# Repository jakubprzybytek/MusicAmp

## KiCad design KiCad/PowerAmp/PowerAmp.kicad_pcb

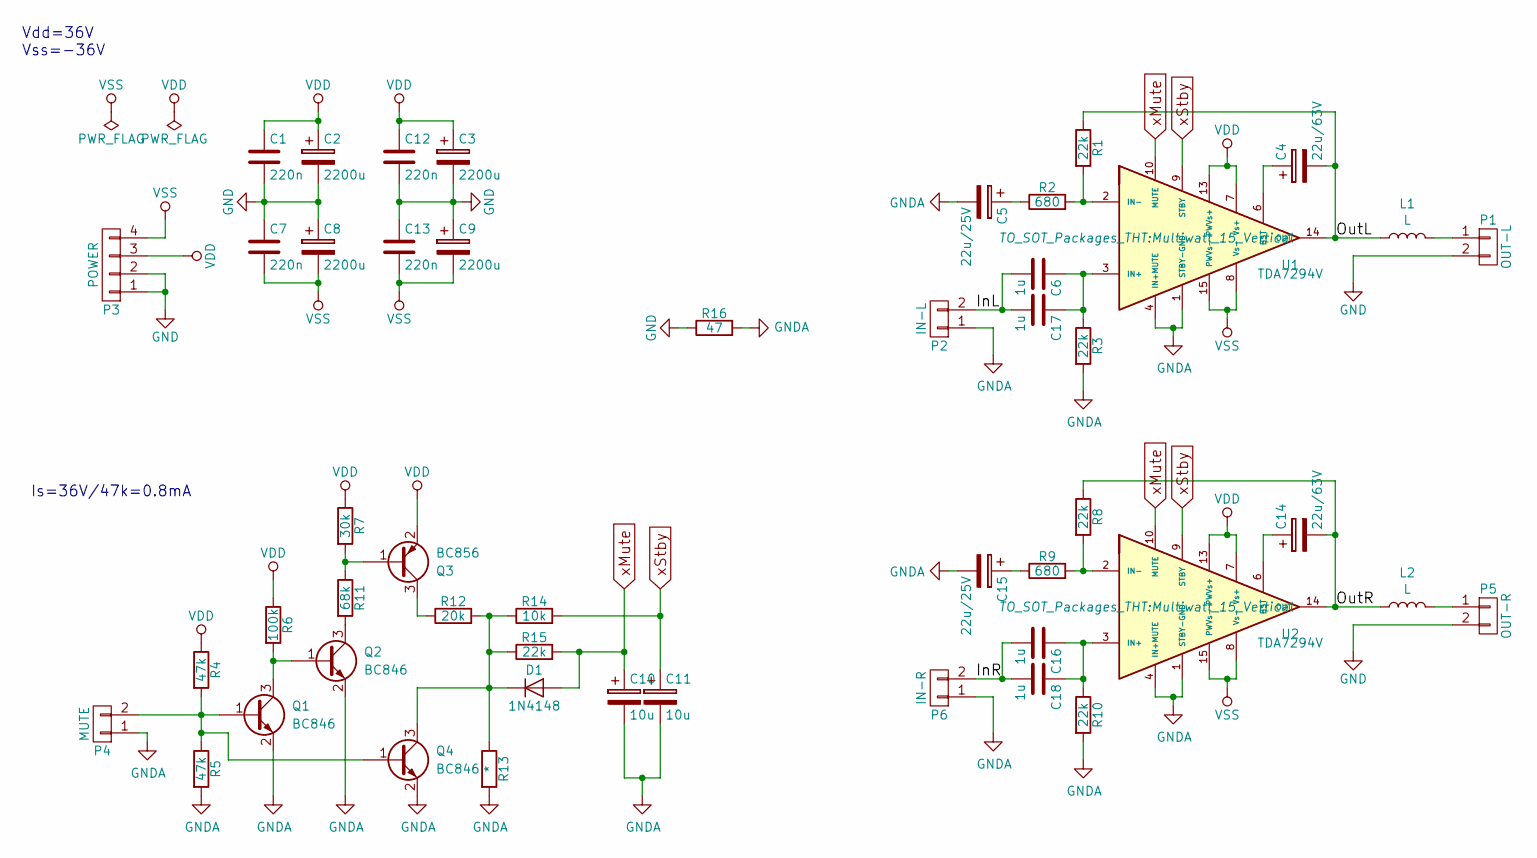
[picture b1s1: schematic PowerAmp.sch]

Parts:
C1, C7, C12, C13: 220n; C_0805_2012Metric
C2, C3, C8, C9: 2200u; CP_Radial_D18.0mm_P7.50mm
C4: 22u/63V; CP_Radial_D5.0mm_P2.00mm
C5, C15: 22u/25V; CP_EIA-6032-28_Kemet-C
C6, C16, C17, C18: 1u; C_2220_5650Metric
C10, C11: 10u; CP_Radial_D5.0mm_P2.00mm
C14: 22u/63V; CP_Radial_D5.0mm_P2.50mm
D1: 1N4148; D_MiniMELF
L1, L2: L; L_Axial_L9.5mm_D4.0mm_P12.70mm_Horizontal_Fastron_SMCC
P1: OUT-L; Molex_Mini-Fit_Jr_5566-02A_2x01_P4.20mm_Vertical
P2: IN-L; Molex_Micro-Latch_53253-0270_1x02_P2.00mm_Vertical
P3: POWER; Molex_Mini-Fit_Jr_5566-04A_2x02_P4.20mm_Vertical
P4: MUTE; Molex_Micro-Latch_53253-0270_1x02_P2.00mm_Vertical
P5: OUT-R; Molex_Mini-Fit_Jr_5566-02A_2x01_P4.20mm_Vertical
P6: IN-R; Molex_Micro-Latch_53253-0270_1x02_P2.00mm_Vertical
Q1, Q2, Q4: BC846; SOT-23
Q3: BC856; SOT-23
R1, R3, R8, R10, R15: 22k; R_0805_2012Metric
R2, R9: 680; R_0805_2012Metric
R4, R5: 47k; R_0805_2012Metric
R6: 100k; R_0805_2012Metric
R7: 30k; R_0805_2012Metric
R11: 68k; R_0805_2012Metric
R12: 20k; R_0805_2012Metric
R13: *; R_0805_2012Metric
R14: 10k; R_0805_2012Metric
R16: 47; R_0805_2012Metric
U1, U2: TDA7294V; Multiwatt_15_Vertical

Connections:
/InL: C6.2, C17.2, P2.2
/InR: C16.2, C18.2, P6.2
/OutL: C4.2, L1.1, R1.1, U1.14 (OUT)
/OutR: C14.2, L2.1, R8.1, U2.14 (OUT)
GND: C1.2, C2.2, C3.2, C7.1, C8.1, C9.1, C12.2, C13.1, P1.2, P3.1, P3.2, P5.2, R16.1
GNDA: C5.2, C10.2, C11.2, C15.2, P2.1, P4.1, P6.1, Q1.2 (E), Q2.2 (E), Q4.2 (E), R3.2, R5.2, R10.2, R13.2, R16.2, U1.1 (STBY-GND), U1.4 (IN+MUTE), U2.1 (STBY-GND), U2.4 (IN+MUTE)
unnamed: C4.1, U1.6 (BST)
unnamed: C5.1, R2.1
unnamed: C14.1, U2.6 (BST)
unnamed: C15.1, R9.1
unnamed: C16.1, C18.1, R10.1, U2.3 (IN+)
unnamed: C6.1, C17.1, R3.1, U1.3 (IN+)
unnamed: D1.1 (K), Q4.3 (C), R12.2, R13.1, R14.1, R15.1
unnamed: L1.2, P1.1
unnamed: L2.2, P5.1
unnamed: P4.2, Q1.1 (B), Q4.1 (B), R4.2, R5.1
unnamed: Q1.3 (C), Q2.1 (B), R6.2
unnamed: Q2.3 (C), R11.2
unnamed: Q3.1 (B), R7.2, R11.1
unnamed: Q3.3 (C), R12.1
unnamed: R1.2, R2.2, U1.2 (IN-)
unnamed: R8.2, R9.2, U2.2 (IN-)
VDD: C1.1, C2.1, C3.1, C12.1, P3.3, Q3.2 (E), R4.1, R6.1, R7.1, U1.7 (Vs+), U1.13 (PWVs+), U2.7 (Vs+), U2.13 (PWVs+)
VSS: C7.2, C8.2, C9.2, C13.2, P3.4, U1.8 (Vs-), U1.15 (PWVs-), U2.8 (Vs-), U2.15 (PWVs-)
xMute: C10.1, D1.2 (A), R15.2, U1.10 (MUTE), U2.10 (MUTE)
xStby: C11.1, R14.2, U1.9 (STBY), U2.9 (STBY)

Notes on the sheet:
Vdd=36V Vss=-36V
Is=36V/47k=0.8mA

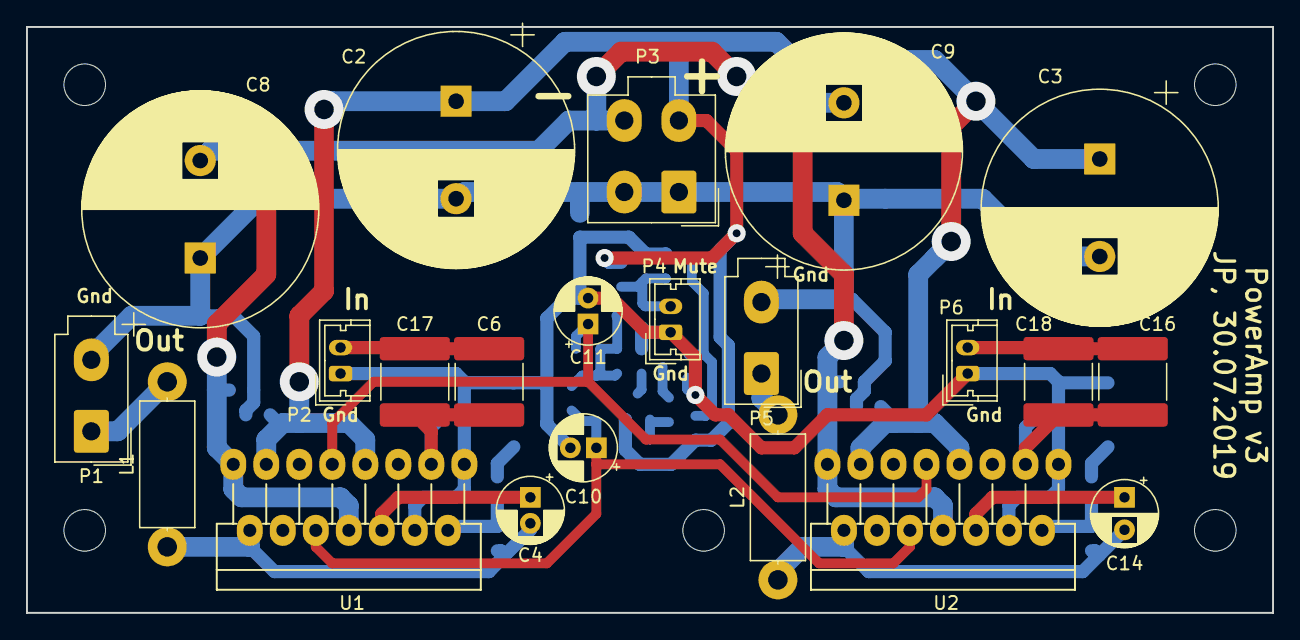
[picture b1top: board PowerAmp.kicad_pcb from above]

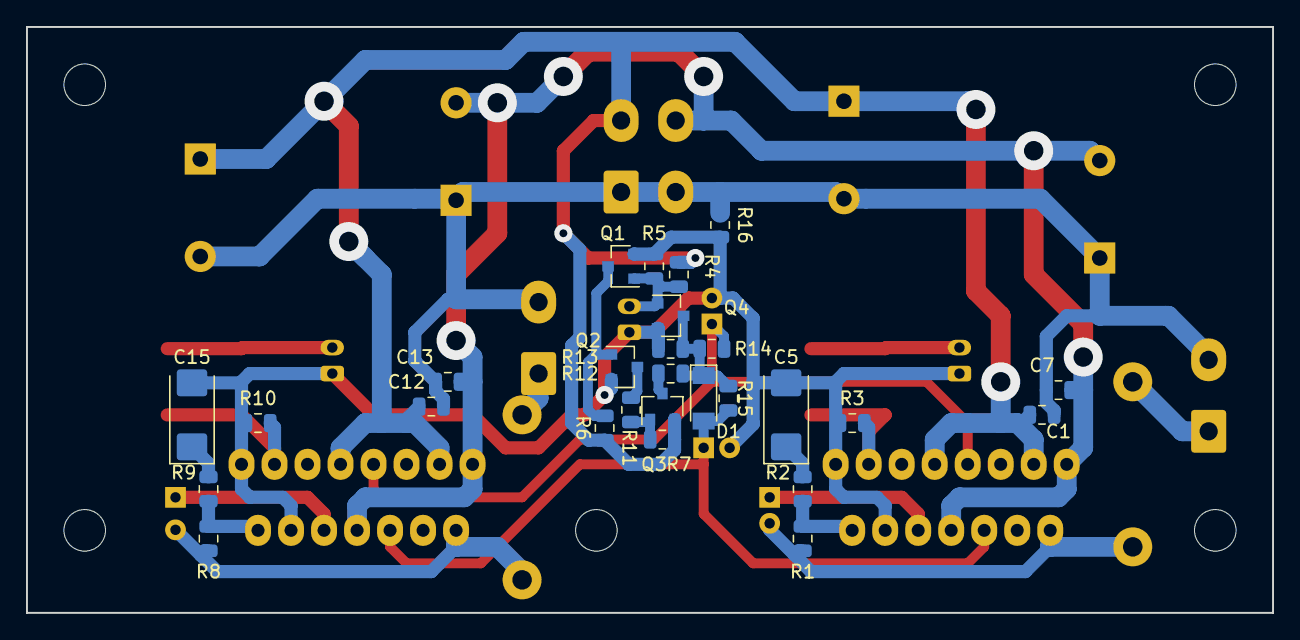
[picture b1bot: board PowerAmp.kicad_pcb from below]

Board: 2 copper layers, 95.9 x 45.1 mm, 49 parts (27 on the bottom side), 26 nets.

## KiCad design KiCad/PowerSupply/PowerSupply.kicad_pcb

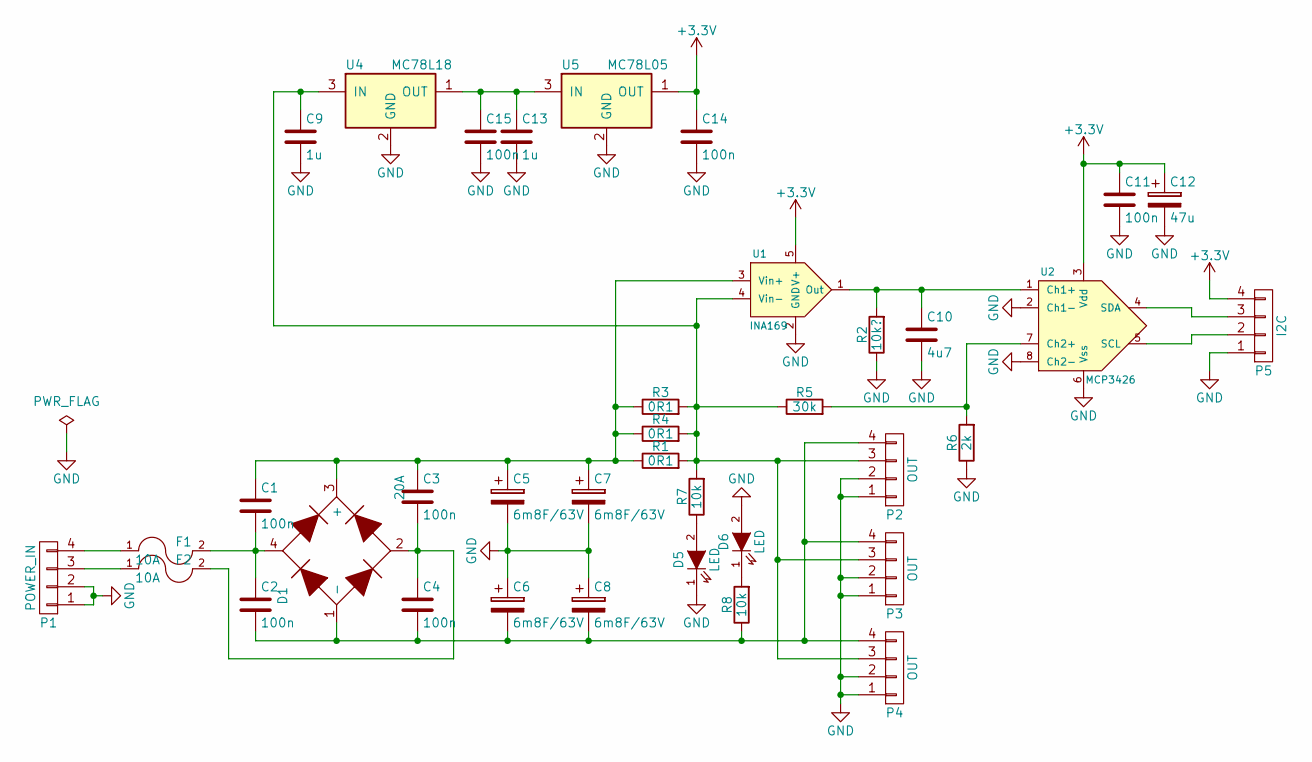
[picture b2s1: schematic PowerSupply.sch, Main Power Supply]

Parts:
C1, C2, C3, C4, C11, C14, C15: 100n; C_0805
C5, C6, C7, C8: 6m8F/63V; C_Radial_D35_L51_P10
C9, C13: 1u; C_0805
C10: 4u7; C_0805
C12: 47u; C_Radial_D5_L6_P2.5
D1: 20A; DiodeBridge
D5, D6: LED; LED-5MM
F1, F2: 10A; Fuseholder5x20_horiz_open_inline_Type-I
P1: POWER_IN; Molex_MiniFit-JR-5556-04A_2x02x4.20mm_Straight
P2, P3, P4: OUT; Molex_MiniFit-JR-5556-04A_2x02x4.20mm_Straight
P5: I2C; Pin_Header_Straight_1x04_Pitch2.54mm
R1, R3, R4: 0R1; R_2512
R2: 10k?; R_0805
R5: 30k; R_0805
R6: 2k; R_0805
R7, R8: 10k; R_0805
U1: INA169; SOT-23-5
U2: MCP3426; SOIC-8_3.9x4.9mm_Pitch1.27mm
U4: MC78L18; SOT89-3_Housing
U5: MC78L05; SOT89-3_Housing

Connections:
+3V3: C11.1, C12.1, C14.1, P5.4, U1.5 (V+), U2.3 (Vdd), U5.1 (OUT)
GND: C5.2, C6.1, C7.2, C8.1, C9.2, C10.2, C11.2, C12.2, C13.2, C14.2, C15.2, D5.1 (K), D6.2 (A), P1.1, P1.2, P2.1, P2.2, P3.1, P3.2, P4.1, P4.2, P5.1, R2.1, R6.1, U1.2 (GND), U2.2 (Ch1-), U2.6 (Vss), U2.8 (Ch2-), U4.2 (GND), U5.2 (GND)
unnamed: C1.1, C3.1, C5.1, C7.1, D1.3 (+), R1.1, R3.1, R4.1, U1.3 (Vin+)
unnamed: C1.2, C2.1, D1.4, F1.2
unnamed: C2.2, C4.2, C6.2, C8.2, D1.1 (-), P2.4, P3.4, P4.4, R8.1
unnamed: C3.2, C4.1, D1.2, F2.2
unnamed: C9.1, P2.3, P3.3, P4.3, R1.2, R3.2, R4.2, R5.1, R7.2, U1.4 (Vin-), U4.3 (IN)
unnamed: C10.1, R2.2, U1.1 (Out), U2.1 (Ch1+)
unnamed: C13.1, C15.1, U4.1 (OUT), U5.3 (IN)
unnamed: D5.2 (A), R7.1
unnamed: D6.1 (K), R8.2
unnamed: F1.1, P1.4
unnamed: F2.1, P1.3
unnamed: P5.2, U2.5 (SCL)
unnamed: P5.3, U2.4 (SDA)
unnamed: R5.2, R6.2, U2.7 (Ch2+)

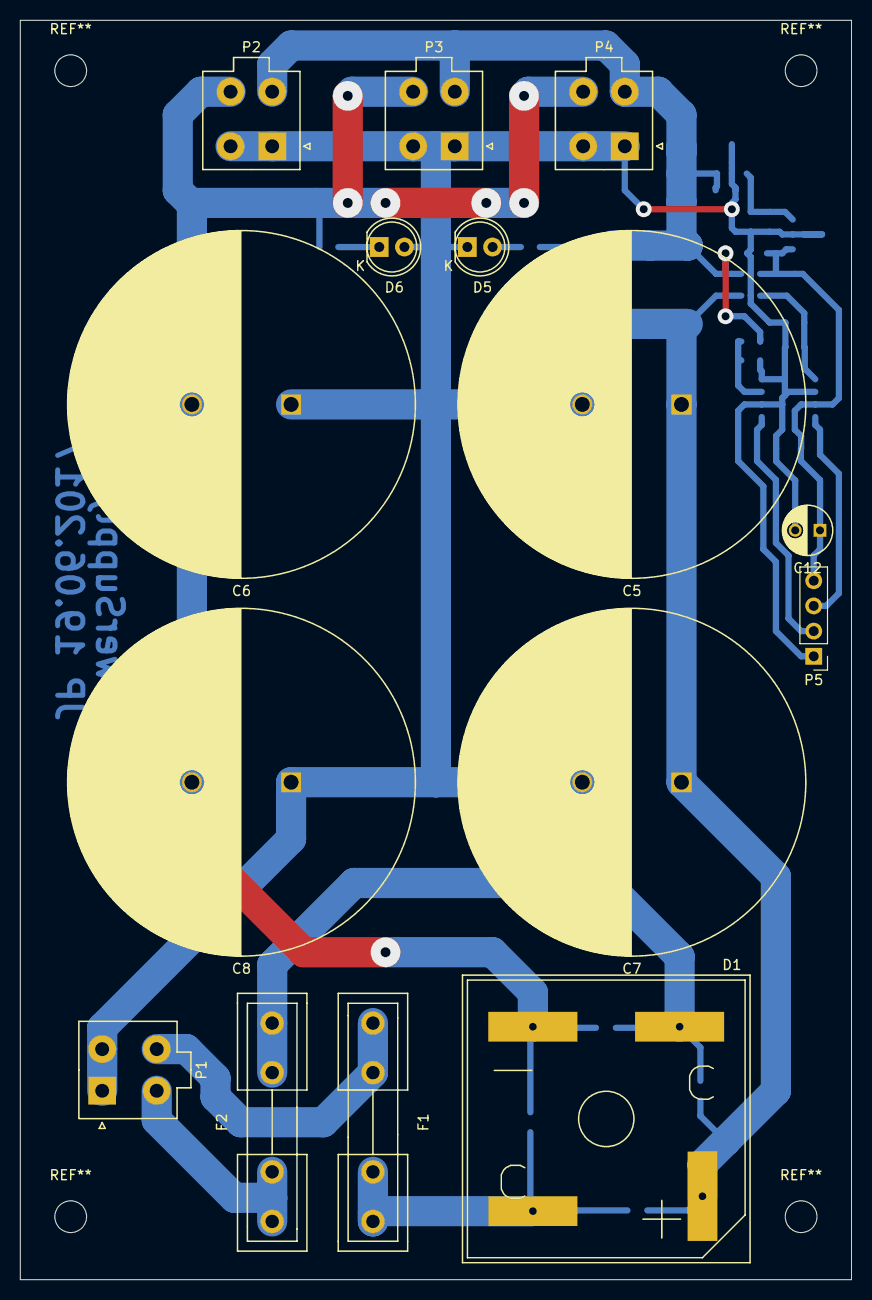
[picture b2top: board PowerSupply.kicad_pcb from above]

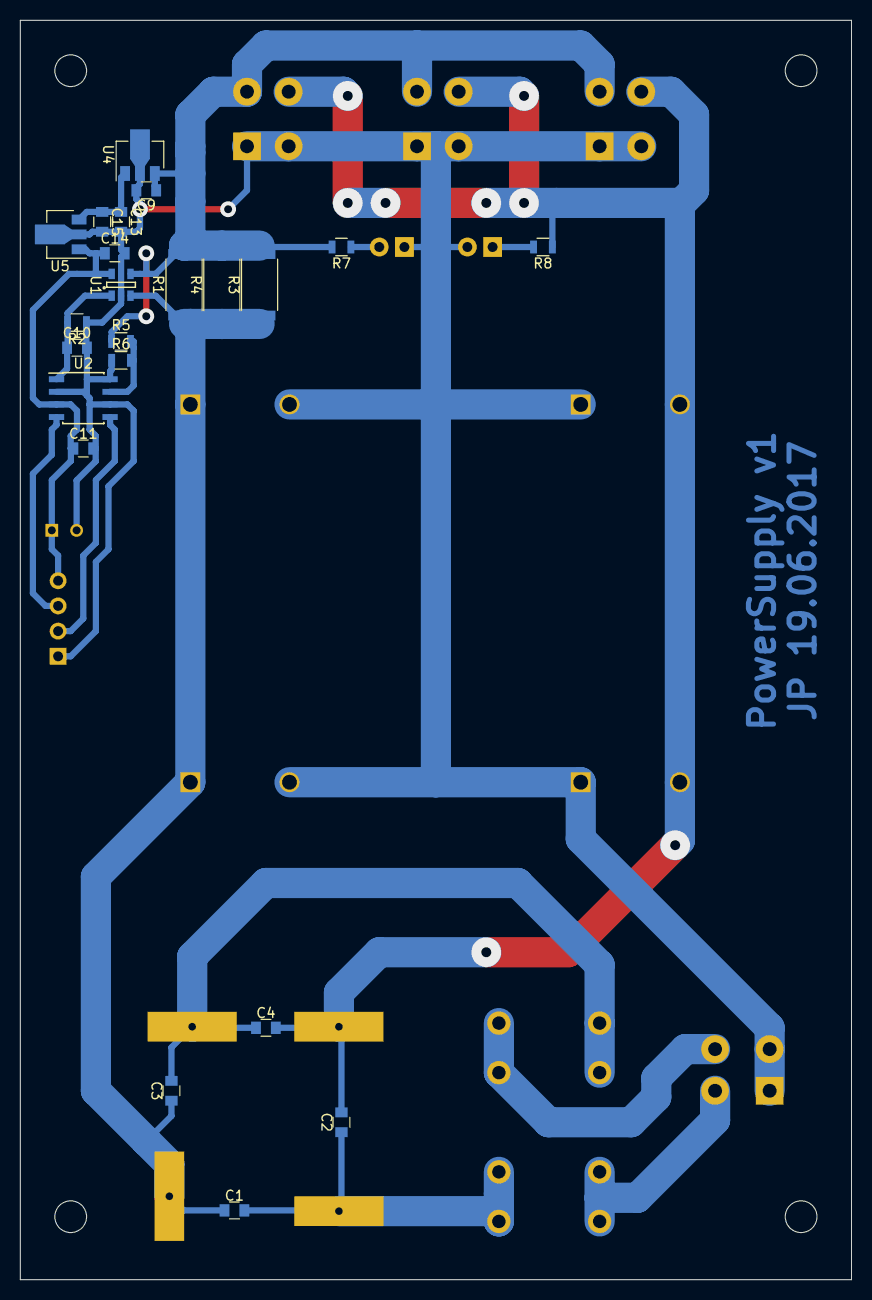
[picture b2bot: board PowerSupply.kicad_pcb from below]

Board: 2 copper layers, 83.8 x 127.0 mm, 37 parts (22 on the bottom side), 16 nets.

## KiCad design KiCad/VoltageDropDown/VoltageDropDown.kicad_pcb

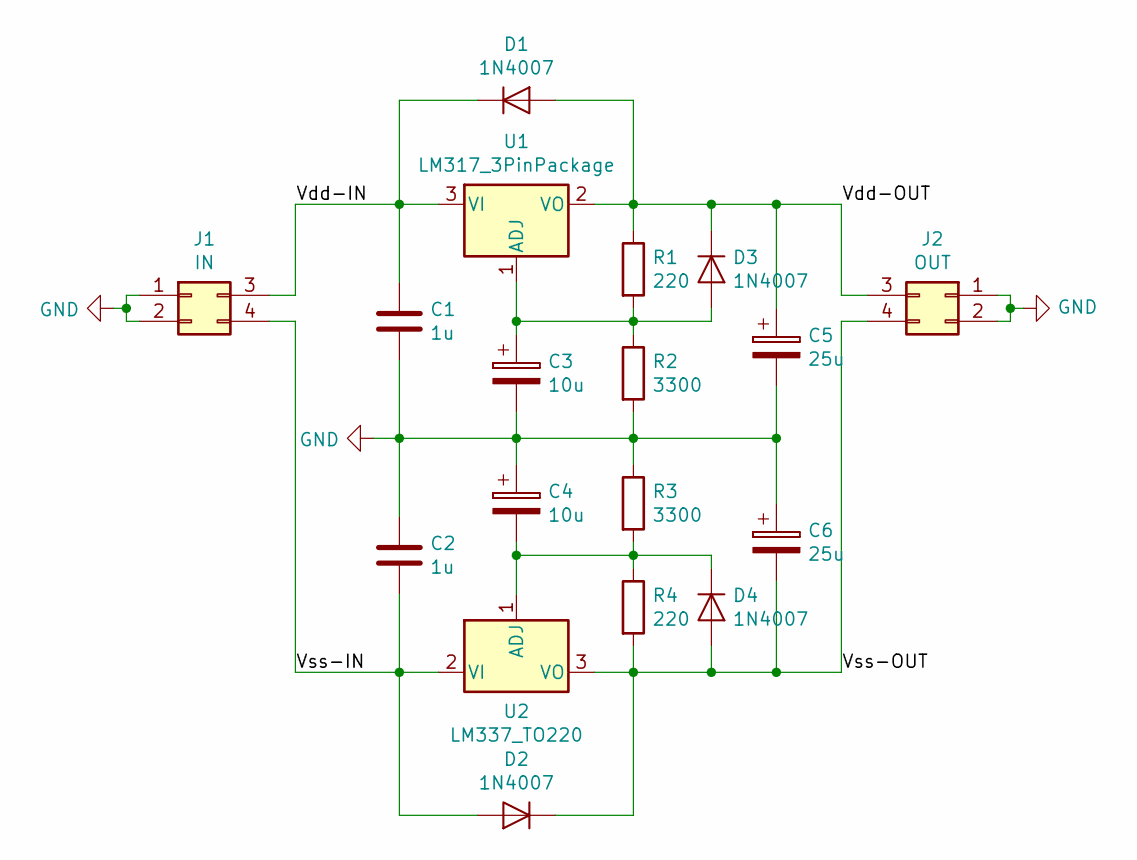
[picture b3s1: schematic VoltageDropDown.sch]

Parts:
C1, C2: 1u; C_Disc_D5.0mm_W2.5mm_P2.50mm
C3, C4: 10u; CP_Radial_D5.0mm_P2.50mm
C5, C6: 25u; CP_Radial_D5.0mm_P2.50mm
D1, D2, D3, D4: 1N4007; D_DO-41_SOD81_P2.54mm_Vertical_AnodeUp
J1: IN; Molex_Mini-Fit_Jr_5566-04A_2x02_P4.20mm_Vertical
J2: OUT; Molex_Mini-Fit_Jr_5566-04A_2x02_P4.20mm_Vertical
R1, R4: 220; R_Axial_DIN0204_L3.6mm_D1.6mm_P2.54mm_Vertical
R2, R3: 3300; R_Axial_DIN0204_L3.6mm_D1.6mm_P2.54mm_Vertical
U1: LM317_3PinPackage; TO-220-3_Vertical
U2: LM337_TO220; TO-220-3_Vertical

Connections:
/Vdd-IN: C1.1, D1.1 (K), J1.3, U1.3 (VI)
/Vdd-OUT: C5.1, D1.2 (A), D3.1 (K), J2.3, R1.1, U1.2 (VO)
/Vss-IN: C2.2, D2.2 (A), J1.4, U2.2 (VI)
/Vss-OUT: C6.2, D2.1 (K), D4.2 (A), J2.4, R4.2, U2.3 (VO)
GND: C1.2, C2.1, C3.2, C4.1, C5.2, C6.1, J1.1, J1.2, J2.1, J2.2, R2.2, R3.1
unnamed: C3.1, D3.2 (A), R1.2, R2.1, U1.1 (ADJ)
unnamed: C4.2, D4.1 (K), R3.2, R4.1, U2.1 (ADJ)

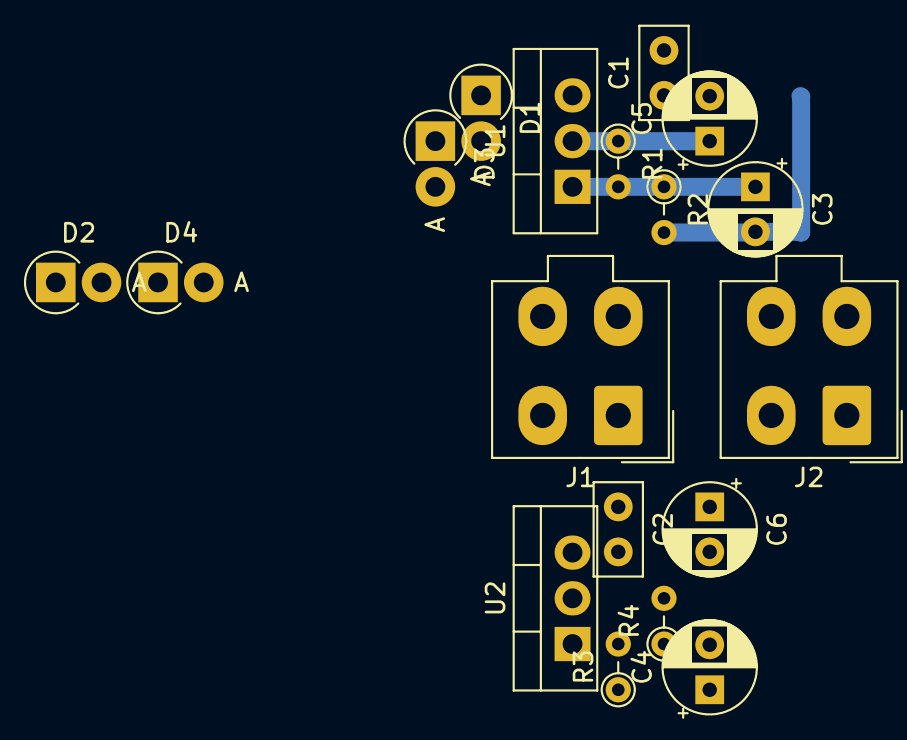
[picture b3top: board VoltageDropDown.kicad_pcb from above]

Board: 2 copper layers, 18 parts (0 on the bottom side), 7 nets.

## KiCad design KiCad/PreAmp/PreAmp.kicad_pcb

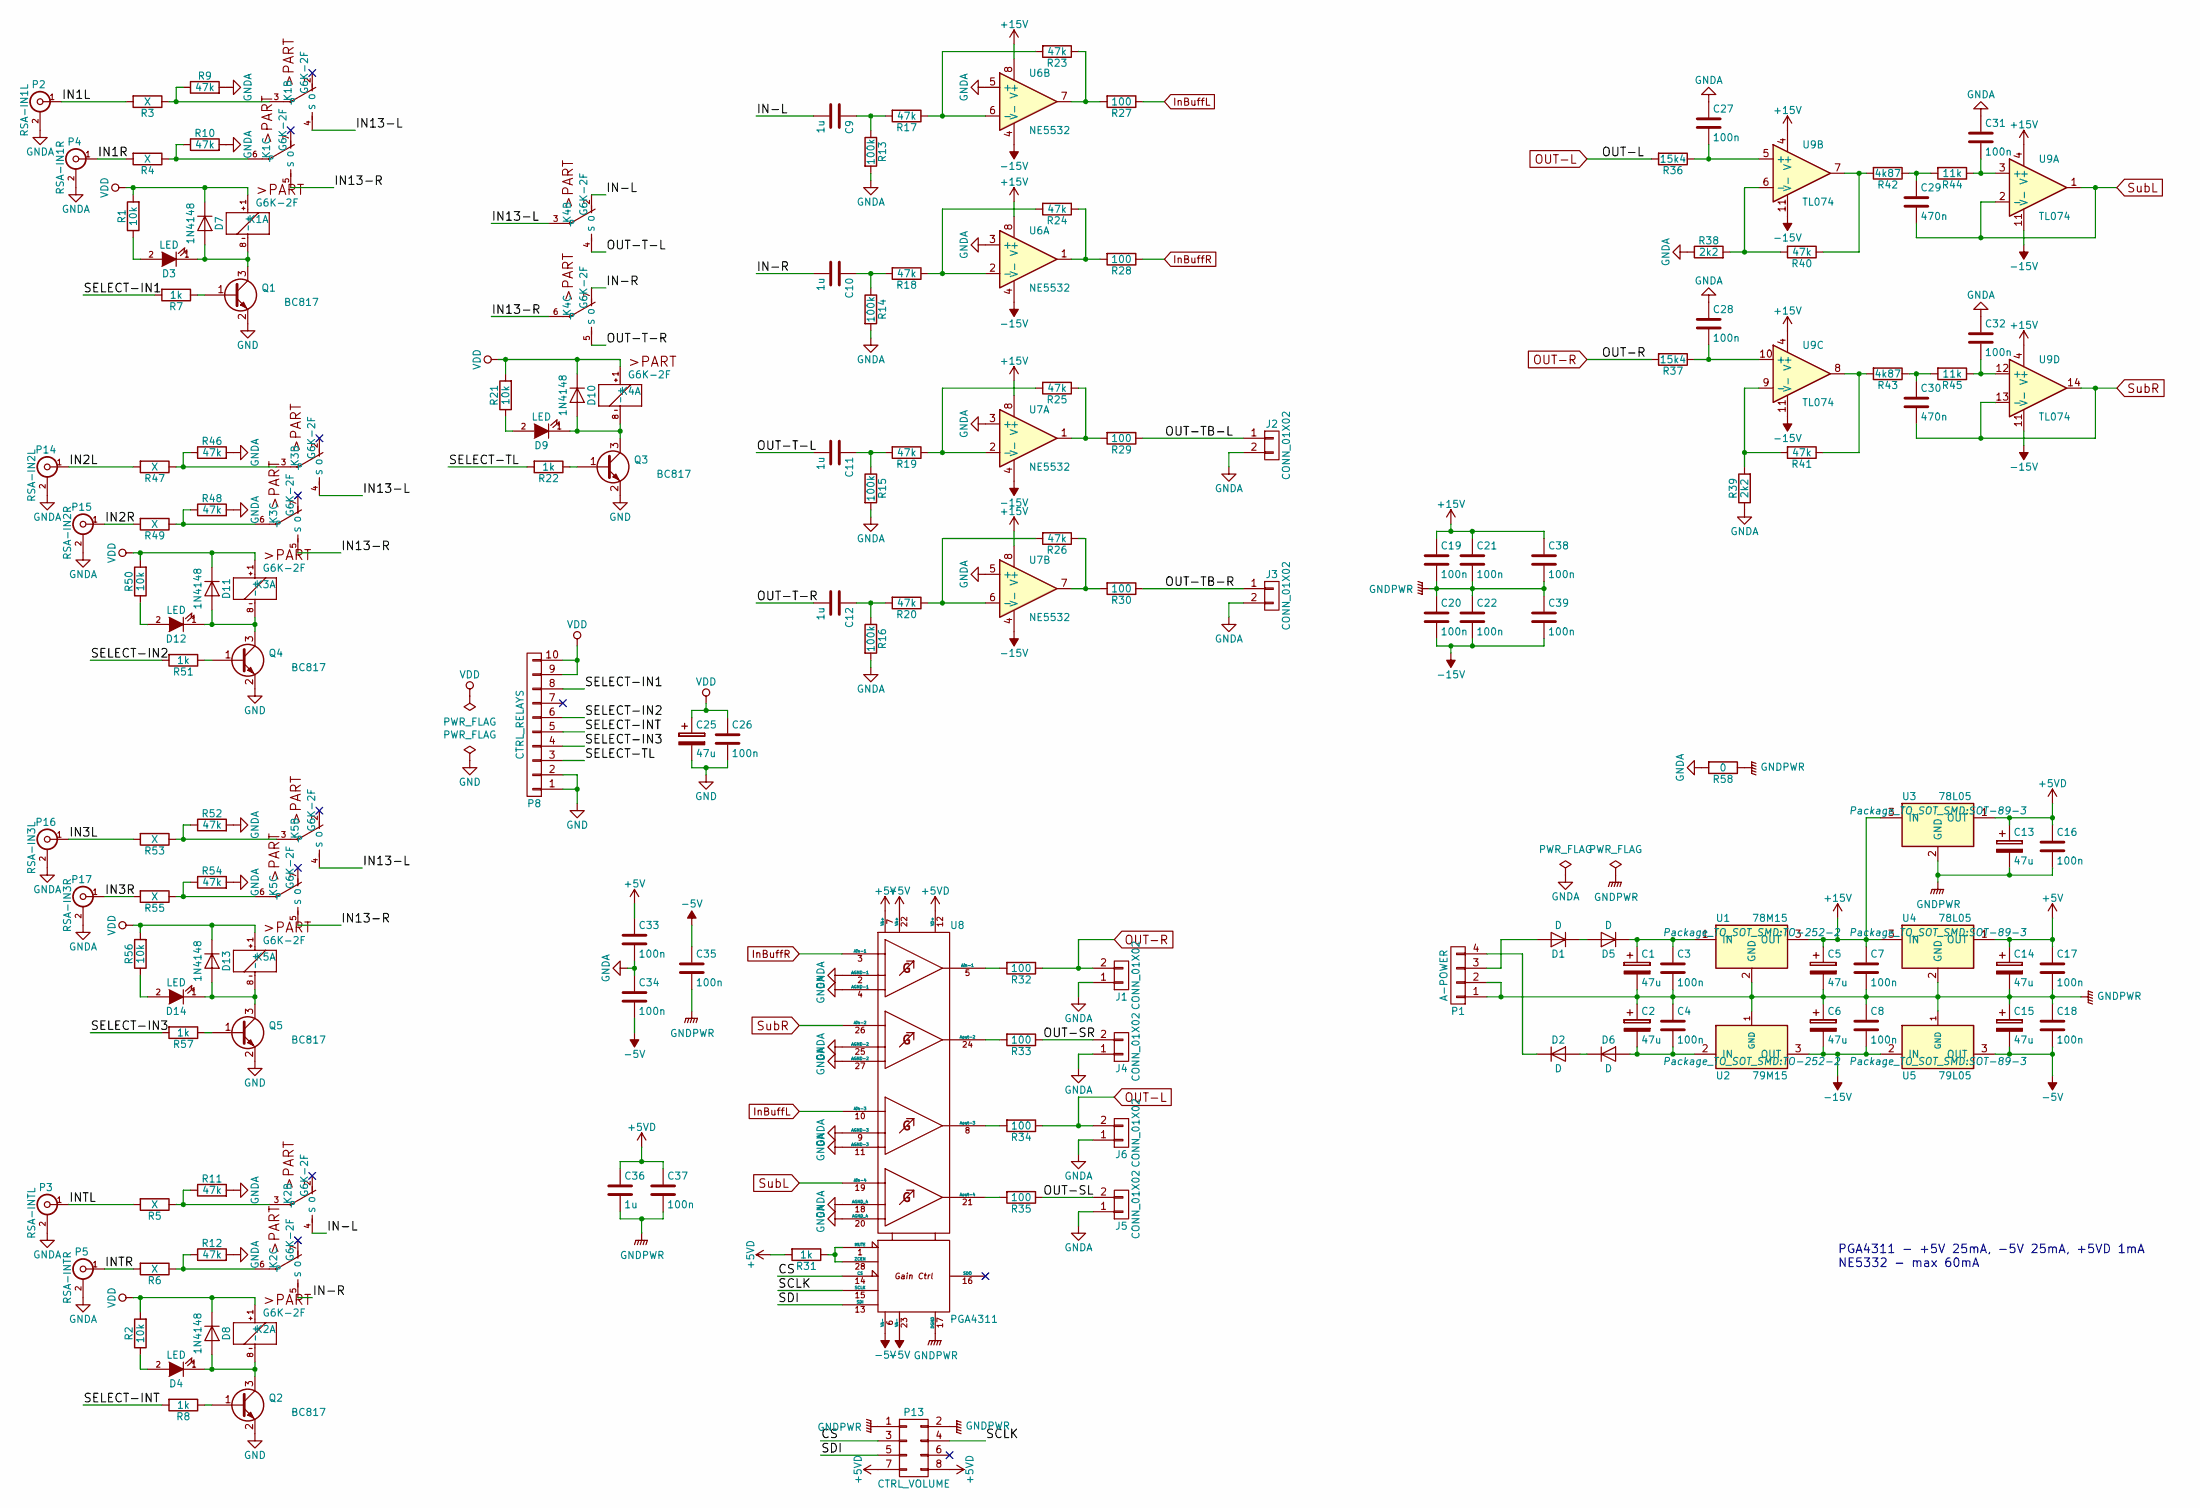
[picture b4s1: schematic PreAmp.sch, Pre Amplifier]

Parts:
C1, C2, C5, C6, C14, C15, C25: 47u; CP_Radial_D6.3mm_P2.50mm
C3, C4, C7, C8, C16, C17, C18, C19, C20, C21, C22, C26, C27, C28, C31, C32, C33, C34, C35, C37, C38, C39: 100n; C_0805_2012Metric
C9, C10, C11, C12, C36: 1u; C_0805_2012Metric
C13: 47u; C_Elec_6.3x5.8
C29, C30: 470n; C_0805_2012Metric
D1, D2, D5, D6: D; D_MELF
D3, D4, D9, D12, D14: LED; LED_0805_2012Metric
D7, D8, D10, D11, D13: 1N4148; D_1206_3216Metric
J1, J4, J5, J6: CONN_01X02; PinHeader_1x02_P2.54mm_Vertical
J2, J3: CONN_01X02; PINHEAD1-2
K1, K2, K3, K4, K5: G6K-2F; relay-G6K-2F
P1: A-POWER; Molex_Mini-Fit_Jr_5566-04A_2x02_P4.20mm_Vertical
P2: RSA-IN1L; PINHEAD1-2
P3: RSA-INTL; PINHEAD1-2
P4: RSA-IN1R; PINHEAD1-2
P5: RSA-INTR; PINHEAD1-2
P8: CTRL_RELAYS; IDC-Header_2x05_P2.54mm_Vertical
P13: CTRL_VOLUME; IDC-Header_2x04_P2.54mm_Vertical
P14: RSA-IN2L; PINHEAD1-2
P15: RSA-IN2R; PINHEAD1-2
P16: RSA-IN3L; PINHEAD1-2
P17: RSA-IN3R; PINHEAD1-2
Q1, Q2, Q3, Q4, Q5: BC817; SOT-23
R1, R2, R21, R50, R56: 10k; R_0805_2012Metric
R3, R4, R5, R6, R47, R49, R53, R55: X; R_0805_2012Metric
R7, R8, R22, R31, R51, R57: 1k; R_0805_2012Metric
R9, R10, R11, R12, R17, R18, R19, R20, R23, R24, R25, R26, R40, R41, R46, R48, R52, R54: 47k; R_0805_2012Metric
R13, R14, R15, R16: 100k; R_0805_2012Metric
R27, R28, R29, R30, R32, R33, R34, R35: 100; R_0805_2012Metric
R36, R37: 15k4; R_0805_2012Metric
R38, R39: 2k2; R_0805_2012Metric
R42, R43: 4k87; R_0805_2012Metric
R44, R45: 11k; R_0805_2012Metric
R58: 0; R_0805_2012Metric
U1: 78M15; TO-252-2
U2: 79M15; TO-252-2
U3, U4: 78L05; SOT-89-3
U5: 79L05; SOT-89-3
U6, U7: NE5532; SOIC-8_3.9x4.9mm_P1.27mm
U8: PGA4311; SOIC-28W_7.5x17.9mm_P1.27mm
U9: TL074; SOIC-14_3.9x8.7mm_P1.27mm

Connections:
+5V: C14.1, C17.1, C33.1, U4.1 (OUT), U8.7 (VA+), U8.22 (VA+)
+5VD: C13.1, C16.1, C36.1, C37.1, P13.7, P13.8, R31.2, U3.1 (OUT), U8.12 (VD+)
+15V: C5.1, C7.1, C19.1, C21.1, C38.1, U1.3 (OUT), U3.3 (IN), U4.3 (IN), U6.8 (V+), U7.8 (V+), U9.4 (V+)
-5V: C15.2, C18.2, C34.2, C35.1, U5.3 (OUT), U8.6 (VA-), U8.23 (VA-)
-15V: C6.2, C8.2, C20.2, C22.2, C39.2, U2.3 (OUT), U5.2 (IN), U6.4 (V-), U7.4 (V-), U9.11 (V-)
/CS: P13.3, U8.14 (CS)
/IN1L: P2.1 (In), R3.2
/IN1R: P4.1 (In), R4.2
/IN2L: P14.1 (In), R47.2
/IN2R: P15.1 (In), R49.2
/IN3L: P16.1 (In), R53.2
/IN3R: P17.1 (In), R55.2
/IN13-L: K1.4 (S), K3.4 (S), K4.3, K5.4 (S)
/IN13-R: K1.5 (S), K3.5 (S), K4.6, K5.5 (S)
/IN-L: C9.2, K2.4 (S), K4.2 (O)
/IN-R: C10.2, K2.5 (S), K4.7 (O)
/INTL: P3.1 (In), R5.2
/INTR: P5.1 (In), R6.2
/OUT-SL: J5.2, R35.1
/OUT-SR: J4.2, R33.1
/OUT-T-L: C11.2, K4.4 (S)
/OUT-T-R: C12.2, K4.5 (S)
/OUT-TB-L: J2.1, R29.1
/OUT-TB-R: J3.1, R30.1
/SCLK: P13.4, U8.15 (SCLK)
/SDI: P13.5, U8.13 (SDI)
/SELECT-IN1: P8.8, R7.2
/SELECT-IN2: P8.6, R51.2
/SELECT-IN3: P8.4, R57.2
/SELECT-INT: P8.5, R8.2
/SELECT-TL: P8.3, R22.2
GND: C25.2, C26.2, P8.1, P8.2, Q1.2 (E), Q2.2 (E), Q3.2 (E), Q4.2 (E), Q5.2 (E)
GNDA: C27.1, C28.1, C31.1, C32.1, C33.2, C34.1, J1.1, J2.2, J3.2, J4.1, J5.1, J6.1, P2.2 (Ext), P3.2 (Ext), P4.2 (Ext), P5.2 (Ext), P14.2 (Ext), P15.2 (Ext), P16.2 (Ext), P17.2 (Ext), R9.2, R10.2, R11.2, R12.2, R13.2, R14.2, R15.2, R16.2, R38.1, R39.1, R46.2, R48.2, R52.2, R54.2, R58.2, U6.3 (+), U6.5 (+), U7.3 (+), U7.5 (+), U8.2 (AGND-1), U8.4 (AGND-1), U8.9 (AGND-3), U8.11 (AGND-3), U8.18 (AGND_4), U8.20 (AGND_4), U8.25 (AGND-2), U8.27 (AGND-2); also elsewhere on the board
GNDPWR: C1.2, C2.1, C3.2, C4.1, C5.2, C6.1, C7.2, C8.1, C13.2, C14.2, C15.1, C16.2, C17.2, C18.1, C19.2, C20.1, C21.2, C22.1, C35.2, C36.2, C37.2, C38.2, C39.1, P1.1, P1.2, P13.1, P13.2, R58.1, U1.2 (GND), U2.1 (GND), U3.2 (GND), U4.2 (GND), U5.1 (GND), U8.17 (DGND)
InBuffL: R27.1, U8.10 (Ain-3)
InBuffR: R28.1, U8.3 (Ain-1)
unnamed: C1.1, C3.1, D5.1 (K), U1.1 (IN)
unnamed: C2.2, C4.2, D6.2 (A), U2.2 (IN)
unnamed: C9.1, R13.1, R17.2
unnamed: C10.1, R14.1, R18.2
unnamed: C11.1, R15.1, R19.2
unnamed: C12.1, R16.1, R20.2
unnamed: C27.2, R36.1, U9.5 (+)
unnamed: C28.2, R37.1, U9.10 (+)
unnamed: C29.1, R42.1, R44.2
unnamed: C30.1, R43.1, R45.2
unnamed: C31.2, R44.1, U9.3 (+)
unnamed: C32.2, R45.1, U9.12 (+)
unnamed: D1.1 (K), D5.2 (A)
unnamed: D1.2 (A), P1.3
unnamed: D2.1 (K), P1.4
unnamed: D2.2 (A), D6.1 (K)
unnamed: D3.1 (K), D7.2 (A), K1.8 (-), Q1.3 (C)
unnamed: D3.2 (A), R1.1
unnamed: D4.1 (K), D8.2 (A), K2.8 (-), Q2.3 (C)
unnamed: D4.2 (A), R2.1
unnamed: D9.2 (A), R21.1
unnamed: D9.1 (K), D10.2 (A), K4.8 (-), Q3.3 (C)
unnamed: D11.2 (A), D12.1 (K), K3.8 (-), Q4.3 (C)
unnamed: D12.2 (A), R50.1
unnamed: D13.2 (A), D14.1 (K), K5.8 (-), Q5.3 (C)
unnamed: D14.2 (A), R56.1
unnamed: K1.3, R3.1, R9.1
unnamed: K1.6, R4.1, R10.1
unnamed: K2.3, R5.1, R11.1
unnamed: K2.6, R6.1, R12.1
unnamed: K3.3, R46.1, R47.1
unnamed: K3.6, R48.1, R49.1
unnamed: K5.3, R52.1, R53.1
unnamed: K5.6, R54.1, R55.1
unnamed: Q1.1 (B), R7.1
unnamed: Q2.1 (B), R8.1
unnamed: Q3.1 (B), R22.1
unnamed: Q4.1 (B), R51.1
unnamed: Q5.1 (B), R57.1
unnamed: R17.1, R23.2, U6.6 (-)
unnamed: R18.1, R24.2, U6.2 (-)
unnamed: R19.1, R25.2, U7.2 (-)
unnamed: R20.1, R26.2, U7.6 (-)
unnamed: R23.1, R27.2, U6.7
unnamed: R24.1, R28.2, U6.1
unnamed: R25.1, R29.2, U7.1
unnamed: R26.1, R30.2, U7.7
unnamed: R31.1, U8.1 (MUTE), U8.28 (ZCEN)
unnamed: R32.2, U8.5 (Ain-1)
unnamed: R33.2, U8.24 (Aout-2)
unnamed: R34.2, U8.8 (Aout-3)
unnamed: R35.2, U8.21 (Aout-4)
unnamed: R38.2, R40.2, U9.6 (-)
unnamed: R39.2, R41.2, U9.9 (-)
unnamed: R40.1, R42.2, U9.7
unnamed: R41.1, R43.2, U9.8
OUT-L: J6.2, R34.1, R36.2
OUT-R: J1.2, R32.1, R37.2
SubL: C29.2, U8.19 (Ain-4), U9.1, U9.2 (-)
SubR: C30.2, U8.26 (Ain-2), U9.13 (-), U9.14
VDD: C25.1, C26.1, D7.1 (K), D8.1 (K), D10.1 (K), D11.1 (K), D13.1 (K), K1.1 (+), K2.1 (+), K3.1 (+), K4.1 (+), K5.1 (+), P8.9, P8.10, R1.2, R2.2, R21.2, R50.2, R56.2

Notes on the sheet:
PGA4311 - +5V 25mA, -5V 25mA, +5VD 1mA NE5332 - max 60mA

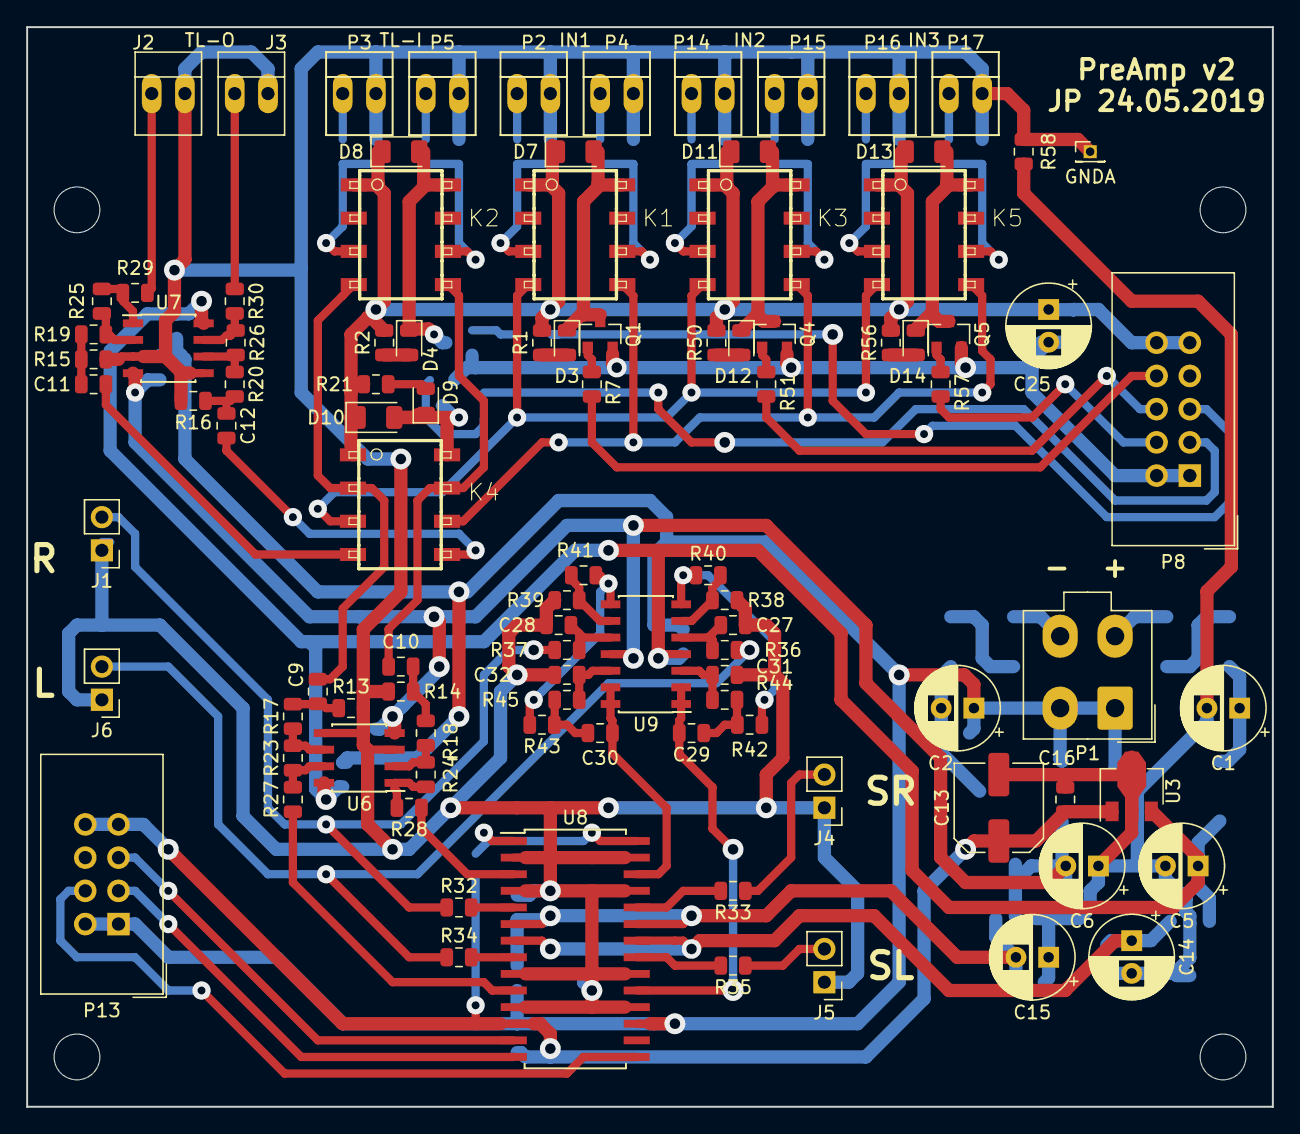
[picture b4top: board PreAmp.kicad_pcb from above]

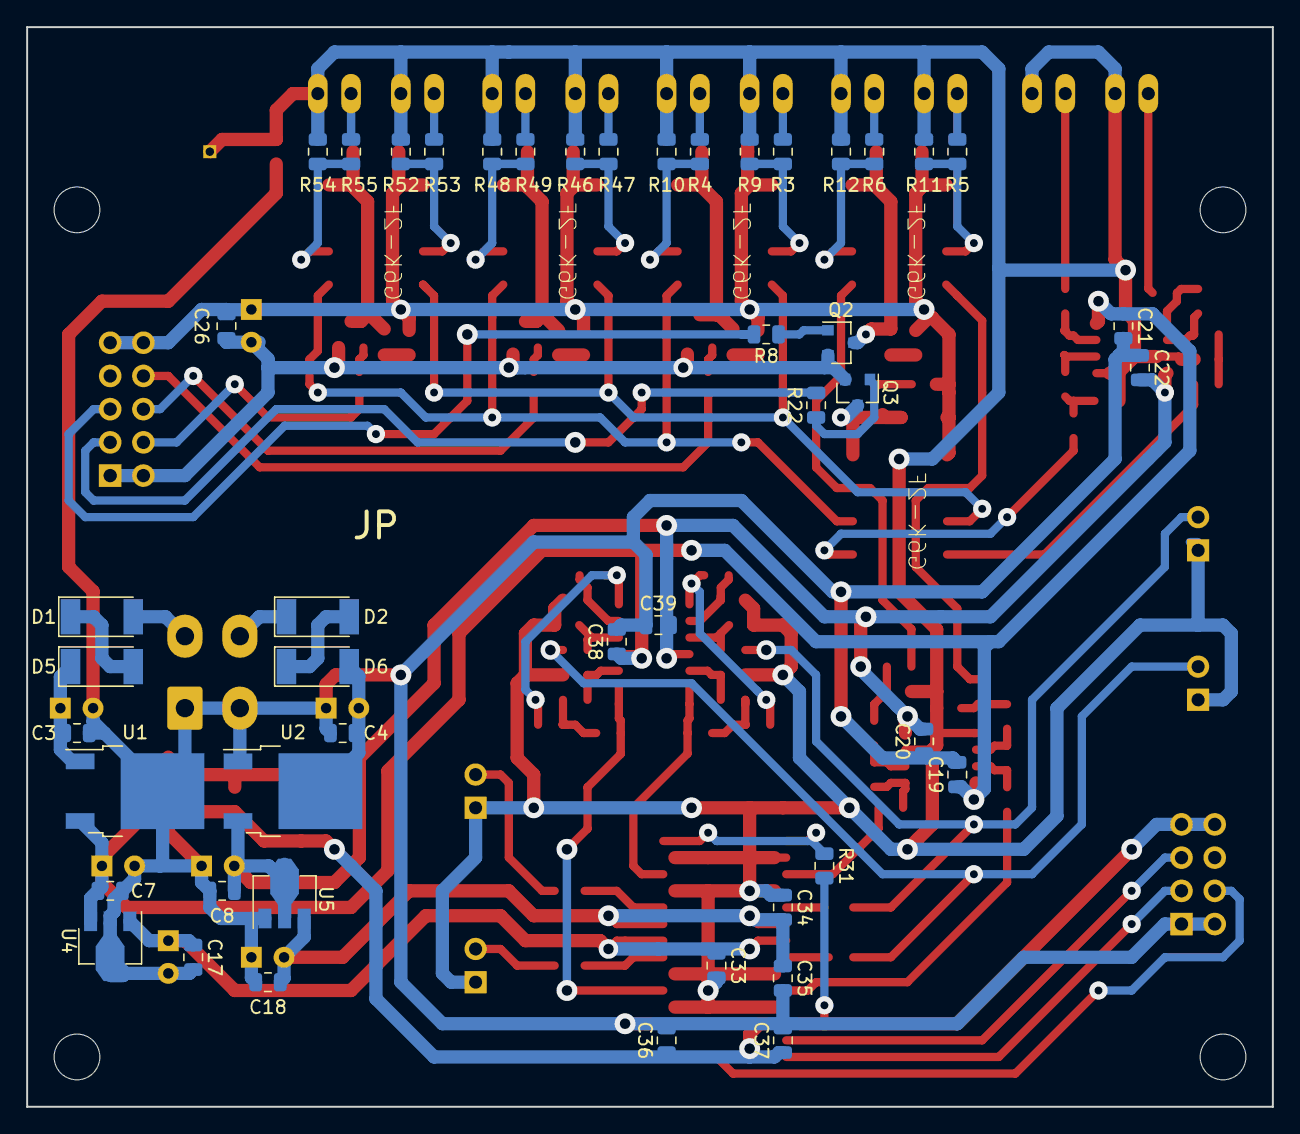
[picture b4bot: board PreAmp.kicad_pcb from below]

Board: 2 copper layers, 95.2 x 82.6 mm, 146 parts (47 on the bottom side), 97 nets.

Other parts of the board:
GNDA: PinHeader_1x01_P1.27mm_Vertical

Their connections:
GNDA: GNDA.1; also elsewhere on the board
